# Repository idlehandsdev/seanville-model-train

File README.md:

# SeanVille Model Train Christmas Ornament (2025)

This is my **2025 Christmas ornament project**.  
A fully self-contained **tiny model train and diorama** designed to fit entirely inside a clear Christmas ornament.

For the full context, design journey, and why some things changed along the way, **watch the video above**.

---

## Overview

The goal of this project was to build a miniature train system that could live inside a Christmas ornament while still feeling like a complete, moving system.

The original concept explored an electronically driven track, using timed control to advance the train around a PCB. As development progressed and real-world constraints showed up, the design pivoted to a **mechanically driven solution** that was simpler, more reliable, and better suited to the timeline.

The current version uses a **tiny mechanical belt system** that moves a magnet beneath the board.  
As the magnet advances, the train follows along the track above.

---

## 🚧 Work in Progress

This project is **still a work in progress**.

- The tiny magnetic track system needs further development
- Motion is currently limited and likely needs more voltage
- Additional tuning is required for smoother and more consistent movement

All of this is discussed in the video, including why the pivot happened and what still needs improvement.

---

## Current Design

- Mechanical belt-driven magnet system
- Train follows the magnet around a fixed loop
- Ornament-sized, self-contained footprint
- Designed for continuous motion and display
- Built with iteration and modularity in mind

Future revisions may revisit electronically driven concepts once reliability and timing constraints are better understood.

---

## Hardware and Parts

- **Controller:** Adafruit ESP32 Feather V2  
- **Lighting:** Adafruit wireless LED coil for flexible, wire-free lighting placement  
- **Mechanical components:** Belts, magnets, bearings, and fasteners sourced from McMaster-Carr  
- **Structure:** Custom 3D printed parts for alignment, mounting, and enclosure  

The project combines off-the-shelf hardware with printed components to keep it accessible while maintaining precision.

---

## Repository Contents

This repository contains design files, firmware, and assets related to the project.

You are encouraged to:
- Modify the design
- Improve the mechanics
- Adapt it for your own ornament, diorama, or tiny controlled environment

If you build one, or make it do something unexpected, I’d love to see it.

---

## Final Notes

Like most engineering projects, this one is shaped by compromise, iteration, and time.

What ships is never the first idea.  
It’s the version that survives.

It’s small.  
It loops.  
It runs quietly in the background.

Which feels appropriate.

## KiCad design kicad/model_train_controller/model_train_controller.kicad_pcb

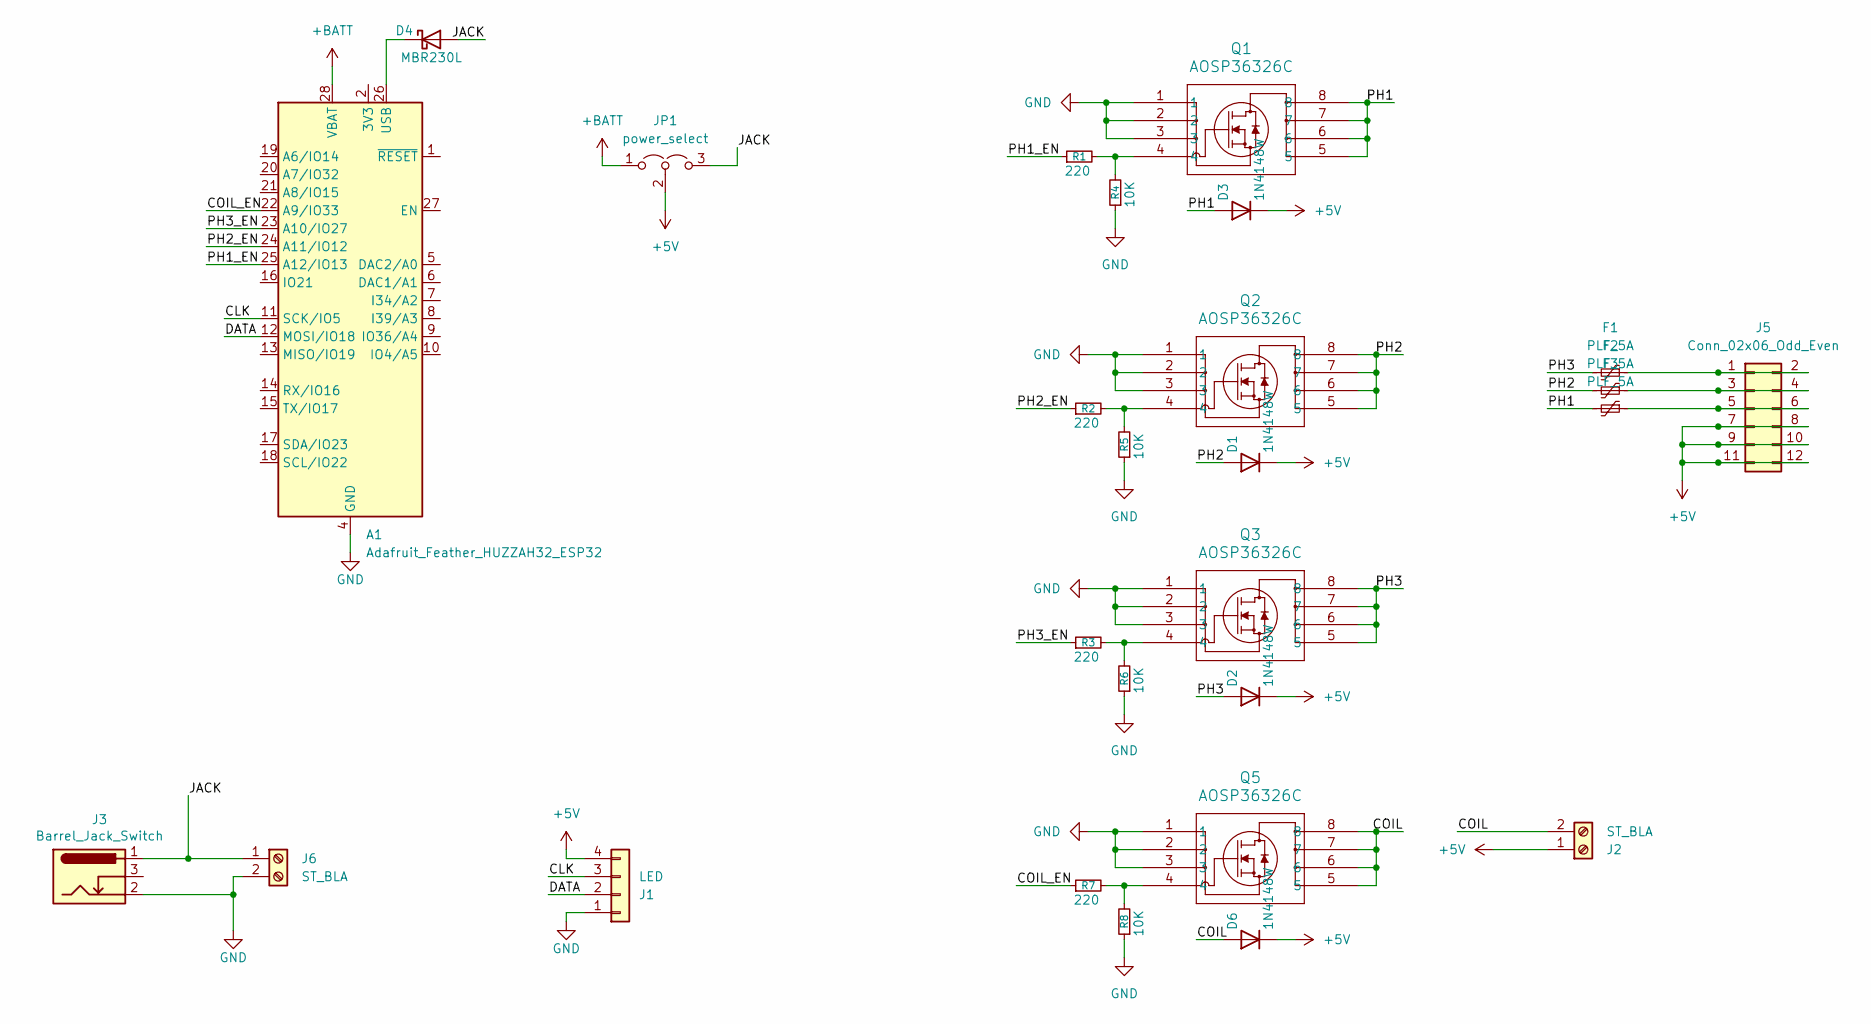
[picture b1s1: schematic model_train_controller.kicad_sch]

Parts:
A1: Adafruit_Feather_HUZZAH32_ESP32; Adafruit_Feather; Digikey Part No. 1528-5477-ND
D1, D2, D3, D6: 1N4148W; D_SOD-123; Digikey Part No. 1N4148W-FDITR-ND
D4: MBR230L; D_SOD-123F; Digikey Part No. MBR230LSFT1GOSCT-ND
F1, F2, F3: PLF_5A; Fuse_1210_3225Metric; Digikey Part No. 118-MF-USML300/6-2CT-ND
J1: LED; TerminalBlock_Phoenix_MPT-0,5-4-2.54_1x04_P2.54mm_Horizontal; Digikey Part No. 732-691210910004-ND
J2, J6: ST_BLA; TerminalBlock_Phoenix_PT-1,5-2-3.5-H_1x02_P3.50mm_Horizontal; Digikey Part No. 277-5719-ND
J3: Barrel_Jack_Switch; BarrelJack_CUI_PJ-063AH_Horizontal; Digikey Part No. CP-063AH-ND
J5: Conn_02x06_Odd_Even; PinHeader_2x06_P2.54mm_Vertical; Digikey Part No. 2057-PH2-12-UA-ND
JP1: power_select; PinHeader_1x03_P2.54mm_Vertical
Q1, Q2, Q3, Q5: AOSP36326C; SO8SOP-8L_AOS; Digikey Part No. 785-AOSP36326CCT-ND
R1, R2, R3, R7: 220; R_0805_2012Metric; Digikey Part No. YAG3711CT-ND
R4, R5, R6, R8: 10K; R_0805_2012Metric; Digikey Part No. 311-10.0KCRTR-ND

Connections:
+5V: D1.1 (K), D2.1 (K), D3.1 (K), D6.1 (K), J1.4, J2.1, J5.7, J5.8, J5.9, J5.10, J5.11, J5.12, JP1.2 (C)
+BATT: A1.28 (VBAT), JP1.1 (A)
/CLK: A1.11 (SCK/IO5), J1.3
/COIL: D6.2 (A), J2.2, Q5.5, Q5.6, Q5.7, Q5.8
/COIL_EN: A1.22 (A9/IO33), R7.1
/DATA: A1.12 (MOSI/IO18), J1.2
/JACK: D4.2 (A), J3.1, J6.1, JP1.3 (B)
/PH1: D3.2 (A), F3.2, Q1.5, Q1.6, Q1.7, Q1.8
/PH1_EN: A1.25 (A12/IO13), R1.1
/PH2: D1.2 (A), F2.2, Q2.5, Q2.6, Q2.7, Q2.8
/PH2_EN: A1.24 (A11/IO12), R2.1
/PH3: D2.2 (A), F1.2, Q3.5, Q3.6, Q3.7, Q3.8
/PH3_EN: A1.23 (A10/IO27), R3.1
GND: A1.4 (GND), J1.1, J3.2, J6.2, Q1.1, Q1.2, Q1.3, Q2.1, Q2.2, Q2.3, Q3.1, Q3.2, Q3.3, Q5.1, Q5.2, Q5.3, R4.1, R5.1, R6.1, R8.1
unnamed: A1.26 (USB), D4.1 (K)
unnamed: F1.1, J5.1, J5.2
unnamed: F2.1, J5.3, J5.4
unnamed: F3.1, J5.5, J5.6
unnamed: Q1.4, R1.2, R4.2
unnamed: Q2.4, R2.2, R5.2
unnamed: Q3.4, R3.2, R6.2
unnamed: Q5.4, R7.2, R8.2

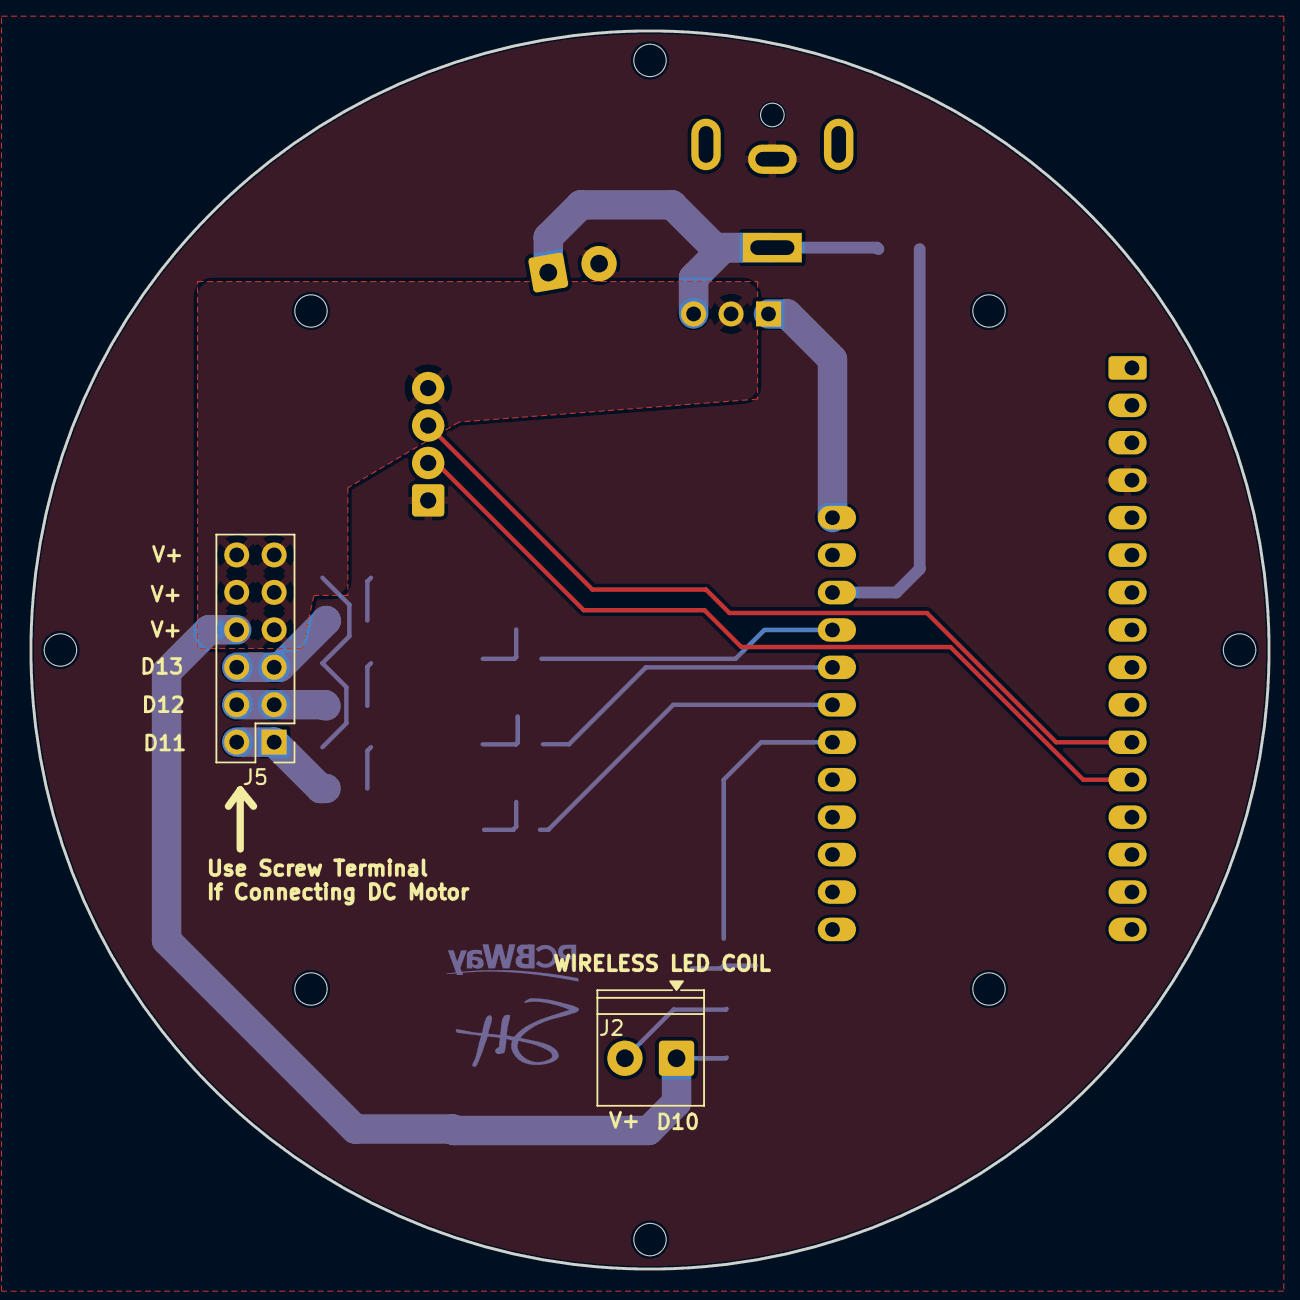
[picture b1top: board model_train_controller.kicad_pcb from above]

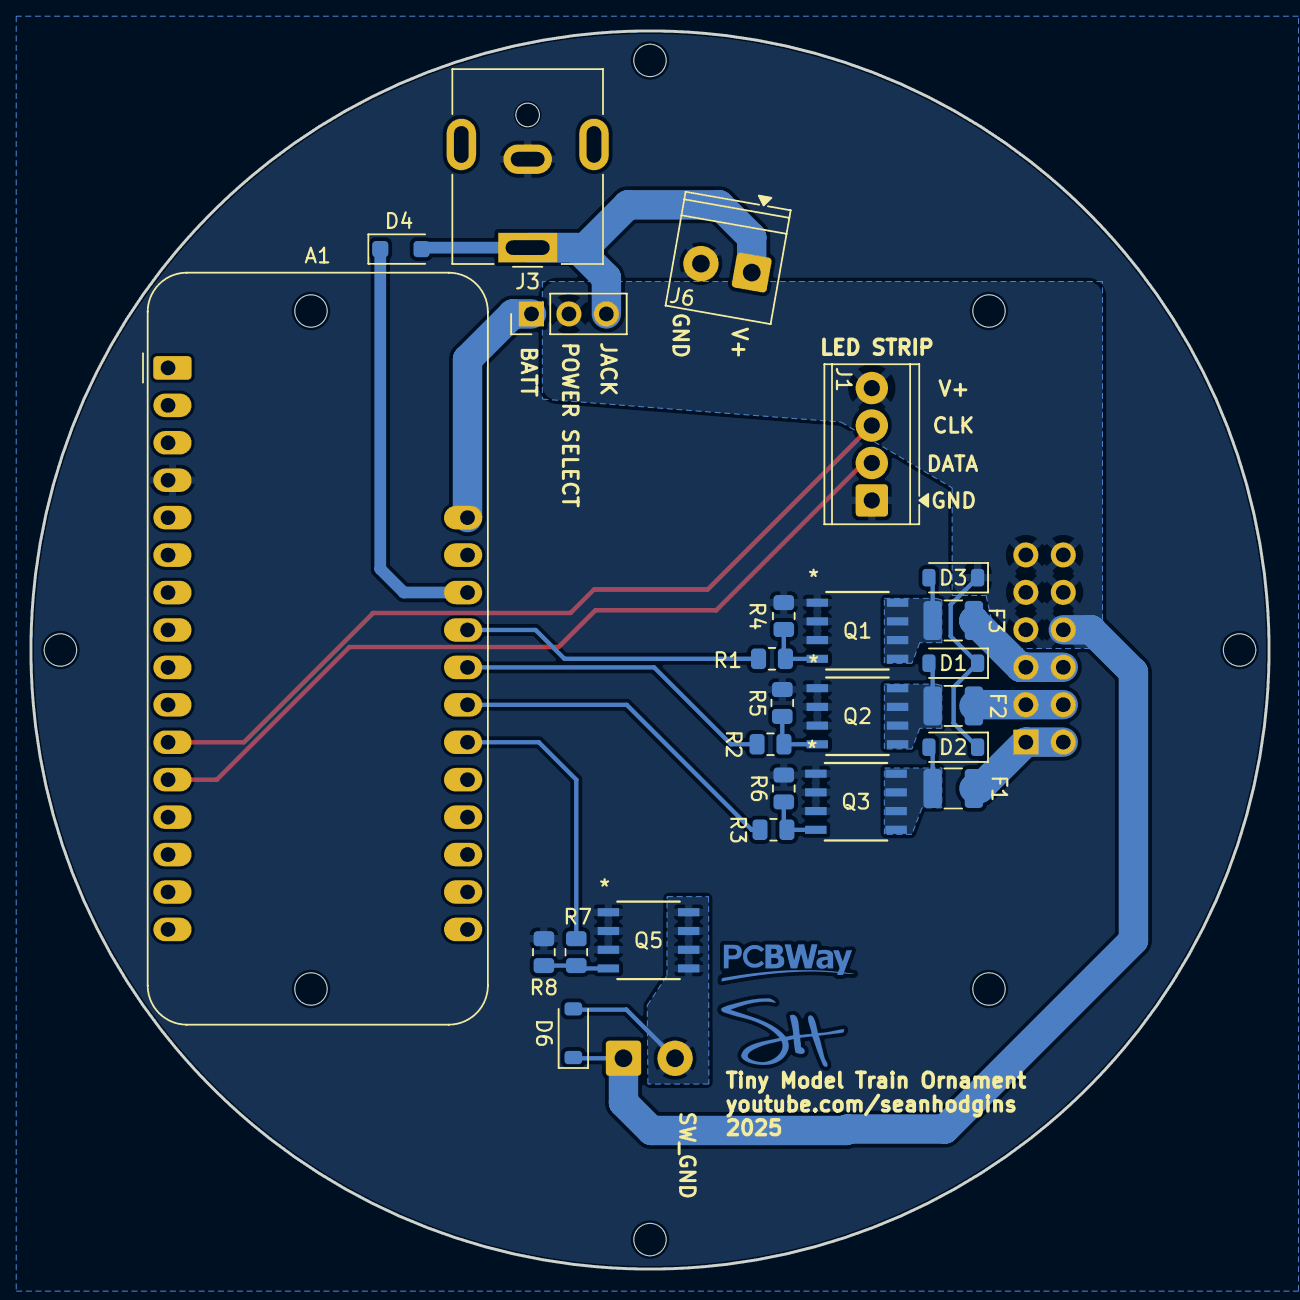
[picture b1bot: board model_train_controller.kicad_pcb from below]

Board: 2 copper layers, 84.0 x 84.0 mm, 27 parts (25 on the bottom side), 22 nets.

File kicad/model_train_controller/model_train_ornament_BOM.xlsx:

|  |  | xxxx xxxx xxxxx xxPCS BOM (Sample Bill of Materials)
Item # | *Designator | *Qty | Manufacturer | *Mfg Part # | Description / Value | *Package/Footprint | Type | Your Instructions / Notes
1.0 | A1 | 1.0 | Adafruit Feather ESP32 V2 |  |  |  | DNP | Feather Headers
2.0 | D1,D2,D3,D6 | 4.0 | Diodes Incorporated | 1N4148W-7-F | DIODE STANDARD 100V 150MA SOD123 | SOD-123 | SMD
3.0 | D4 | 1.0 | onsemi | MBR230LSFT1G | DIODE SCHOTTKY 30V 2A SOD123FL | SOD-123F | SMD
4.0 | F1,F2,F3 | 3.0 | Bourns Inc. | MF-USML300/6-2 | PTC RESET FUSE 6V 3A 1210 | 1210 (3225 Metric) | SMD
5.0 | J1 | 1.0 | Würth Elektronik | 6.91210910004E11 | TERM BLOCK 4P HORIZON 2.54MM PCB | 4 Position Wire to Board Terminal Block | Through Hole
6.0 | J2,J6 | 2.0 | Phoenix Contact | 1751248.0 | TERM BLK 2POS SIDE ENT 3.5MM PCB | 2 Position Wire to Board Terminal Block | Through Hole
7.0 | J3 | 1.0 | Same Sky (Formerly CUI Devices) | PJ-063AH | CONN PWR JACK 2X5.5MM SOLDER | Power Barrel Connector Jack 2.10mm ID (0.083"), 5.50mm OD (0.217") | Through Hole
8.0 | J5 | 1.0 | Phoenix Contact | 1725698.0 | TERM BLK 6P SIDE ENT 2.54MM PCB | 6 Position Wire to Board Terminal Block | DNP | Refer to Image for Populating(leave for customer)
9.0 | JP1 | 1.0 | Molex | 2.2285034E7 | CONN HEADER VERT 3POS 2.54MM | Connector Header Through Hole 3 position 0.100" | Through Hole
10.0 | Q1,Q2,Q3,Q5 | 4.0 | Alpha & Omega Semiconductor Inc. | AOSP36326C | MOSFET N-CH 30V 12A 8SOIC | 8-SOIC | SMD
11.0 | R1,R2,R3,R7 | 4.0 | YAGEO | AC0805FR-07220RL | 220 Ohms ±1% 0.125W, 1/8W Chip Resistor 0805 (2012 Metric) | 0805 (2012 Metric) | SMD
12.0 | R4,R5,R6,R8 | 4.0 | YAGEO | RC0805FR-0710KL | 10 kOhms ±1% 0.125W, 1/8W Chip Resistor | 0805 (2012 Metric) | SMD
Need a quick and accurante quote? Need an efficient production? Please read SMT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
Click for Instructions on How to Create a BOM

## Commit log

2025-12-26 Revise README for Tiny Model Train Christmas Ornament
    Updated README to reflect 2025 project details and design changes.
2025-12-26 Change project title to 'SeanVille Model Train'
    Updated project title in README.
2025-12-26 Initial file commit
2025-12-27 initial CAD file commit
2025-12-27 updated PBC Files and BOM
